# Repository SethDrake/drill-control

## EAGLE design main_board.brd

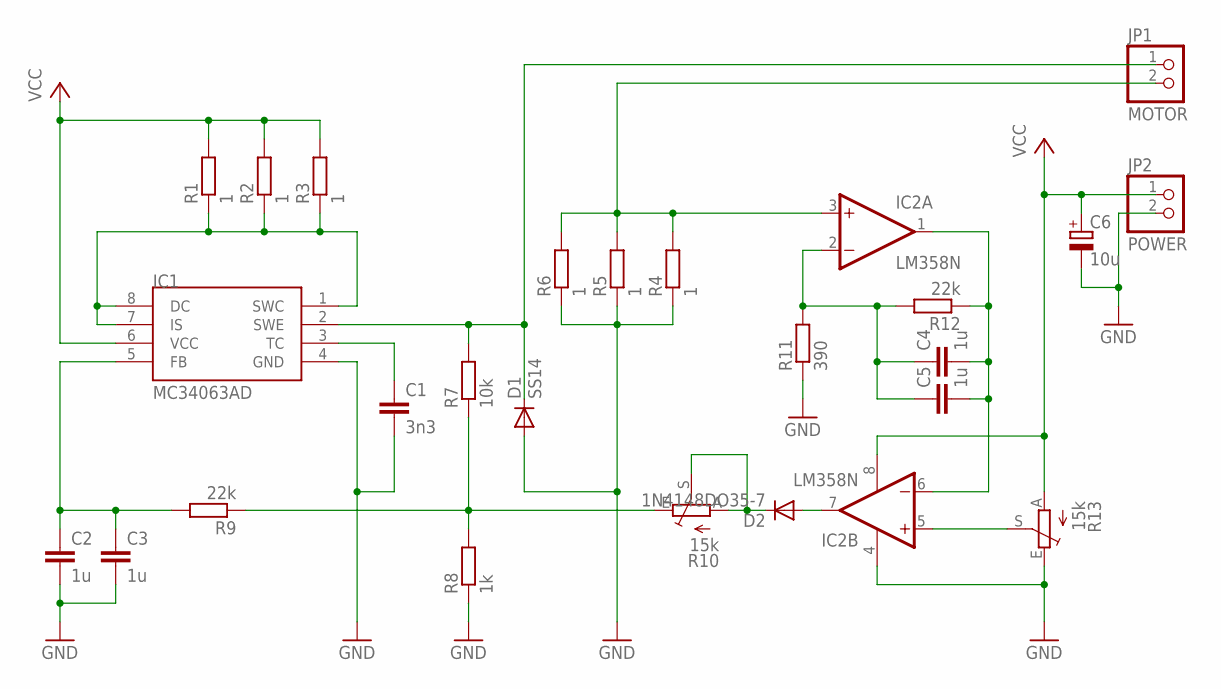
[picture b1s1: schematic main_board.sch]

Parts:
C1: 3n3; C0805
C2, C3, C4, C5: 1u; C0805
C6: 10u; CT6032
D1: SS14; DO214AC
D2: 1N4148DO35-7; DO35-7
IC1: MC34063AD; SOIC8
IC2: LM358N; DIL08
JP1: MOTOR; 1X02
JP2: POWER; 1X02
R1, R2, R3, R4, R5, R6: 1; R0805
R7: 10k; R0805
R8: 1k; R0805
R9, R12: 22k; R0805
R10, R13: 15k; CA6V
R11: 390; R0805

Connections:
GND: C1.2, C2.2, C3.2, C6.-, D1.A, IC1.4 (GND), IC2.4 (V-), JP2.2, R4.1, R5.1, R6.1, R8.1, R11.1, R13.E
unnamed: IC1.1 (SWC), IC1.7 (IS), IC1.8 (DC), R1.1, R2.1, R3.1
unnamed: C1.1, IC1.3 (TC)
unnamed: D2.C, R10.A, R10.S
unnamed: D1.C, IC1.2 (SWE), JP1.1, R7.2
unnamed: C2.1, C3.1, IC1.5 (FB), R9.2
unnamed: C4.1, C5.1, IC2.2 (-IN), R11.2, R12.2
unnamed: IC2.3 (+IN), JP1.2, R4.2, R5.2, R6.2
unnamed: IC2.5 (+IN), R13.S
unnamed: R7.1, R8.2, R9.1, R10.E
unnamed: C4.2, C5.2, IC2.1 (OUT), IC2.6 (-IN), R12.1
unnamed: D2.A, IC2.7 (OUT)
VCC: C6.+, IC1.6 (VCC), IC2.8 (V+), JP2.1, R1.2, R2.2, R3.2, R13.A

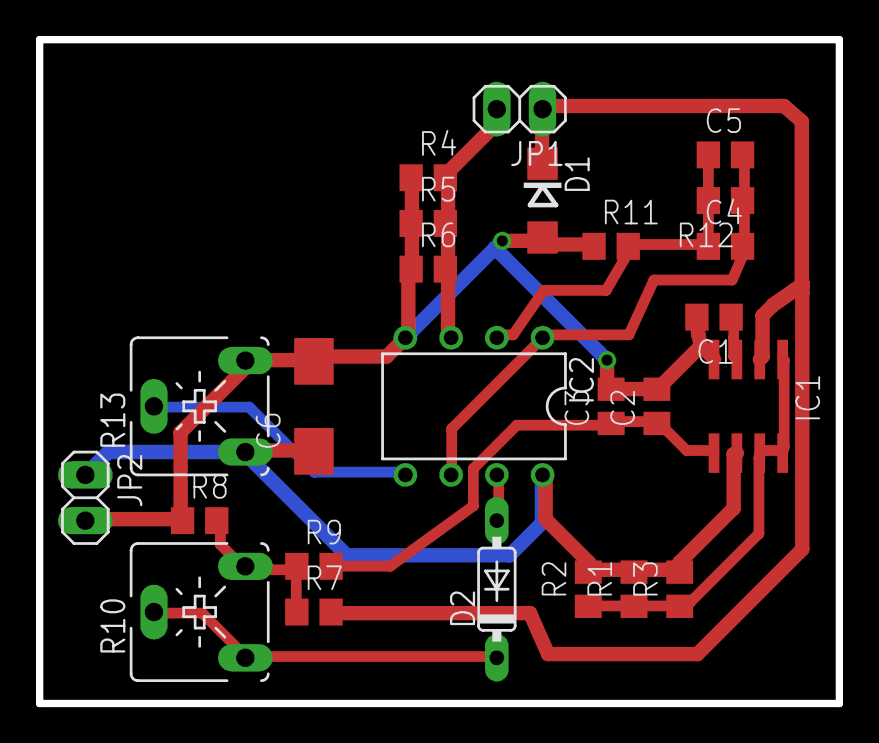
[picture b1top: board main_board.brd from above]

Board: 2 copper layers, 44.4 x 36.9 mm, 25 parts (0 on the bottom side), 13 nets.

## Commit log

2018-10-24 routed pcb
2018-10-24 pcb completed
2018-10-28 completed pcb
